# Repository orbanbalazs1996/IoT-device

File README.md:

# IoT-device
Lokális hálózatba szervezhető mérőpont tervezési fileok, reprezentéló oldalak.
Weboldal:
https://beta.dev.itk.ppke.hu/webprog/~orbba2/fooldal
Weboldal forráskód:
webpage_source.zip
Tok:
https://gmail851013.autodesk360.com/g/shares/SH919a0QTf3c32634dcfc6deb44a4809d65b?viewState=NoIgbgDAdAjCA0IDeAdEAXAngBwKZoC40ARXAZwEsBzAOzXjQEMyzd1C0YAzGAJgBMAzLgDGAWhgAWXAFYxk3pIhiAHJJEr5ATgBGO-o0mSAbCJha0AXxABdIA
Vezérlő programkód:
final.ino:
Tok nyomtatási file:
PCB_case.f3z
Mért adatok:
measured_data.zip
Képek:
pictures.zip
Kapcsolási tervrajz:
schema.sch
PCB tervrajz:
schema.brd

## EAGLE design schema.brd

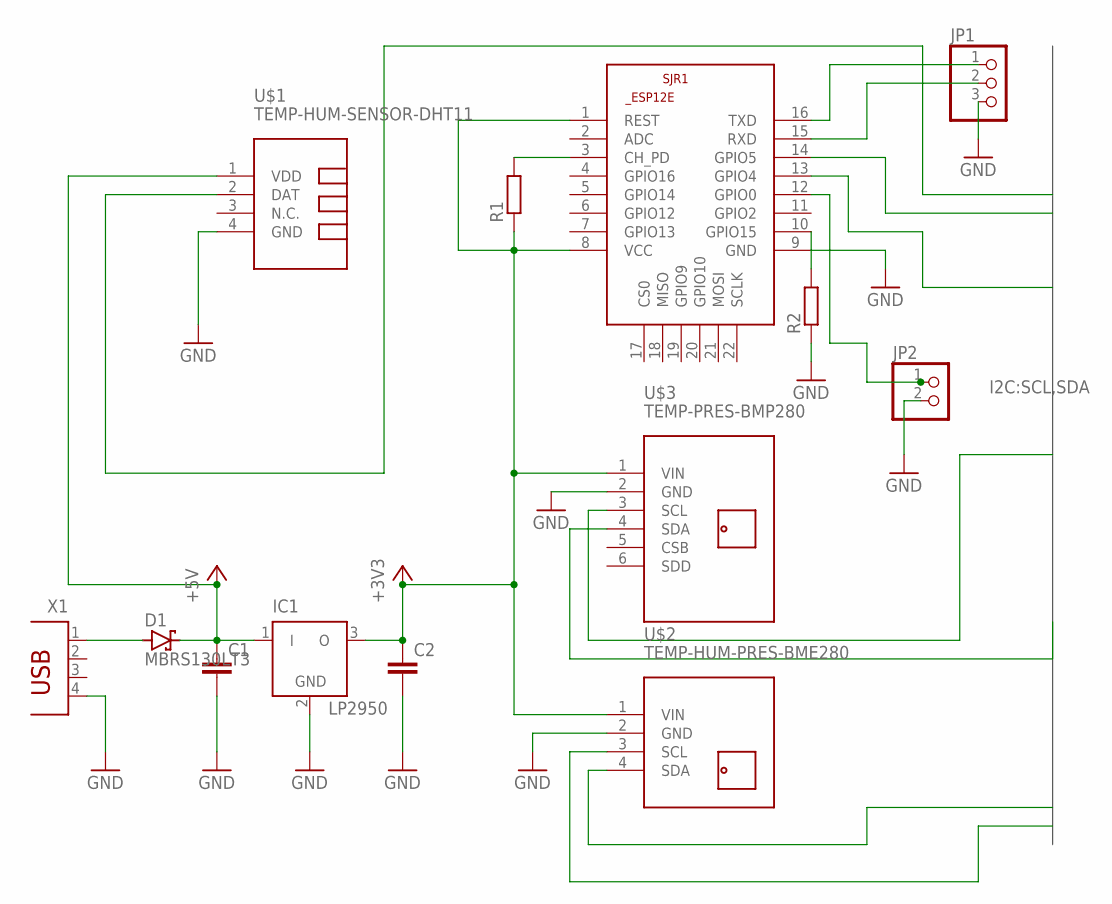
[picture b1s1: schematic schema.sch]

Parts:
C1, C2: C-EUC0603; C0603
D1: MBRS130LT3; SMB
IC1: LP2950; DPACK
JP1: PINHD-1X3; 1X03
JP2: PINHD-1X2; 1X02
R1, R2: R-EU_R0603; R0603
SJR1: ESP8266-12EESP12E; ESP8266-ESP12E
U$1: TEMP-HUM-SENSOR-DHT11
U$2: TEMP-HUM-PRES-BME280
U$3: TEMP-PRES-BMP280
X1: PN61729

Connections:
+3V3: C2.1, IC1.3 (O), R1.1, SJR1.1 (REST), SJR1.8 (VCC), U$2.1 (VIN), U$3.1 (VIN)
+5V: C1.1, D1.C, IC1.1 (I), U$1.1 (VDD)
GND: C1.2, C2.2, IC1.2 (GND), JP1.3, JP2.2, R2.1, SJR1.9 (GND), U$1.4 (GND), U$2.2 (GND), U$3.2 (GND), X1.4
unnamed: R1.2, SJR1.3 (CH_PD)
unnamed: JP2.1, SJR1.12 (GPIO0)
unnamed: D1.A, X1.1
unnamed: JP1.1, SJR1.16 (TXD)
unnamed: JP1.2, SJR1.15 (RXD)
unnamed: R2.2, SJR1.10 (GPIO15)
SCL: SJR1.14 (GPIO5), U$2.3 (SCL), U$3.3 (SCL)
SDA: SJR1.13 (GPIO4), U$1.2 (DAT), U$2.4 (SDA), U$3.4 (SDA)

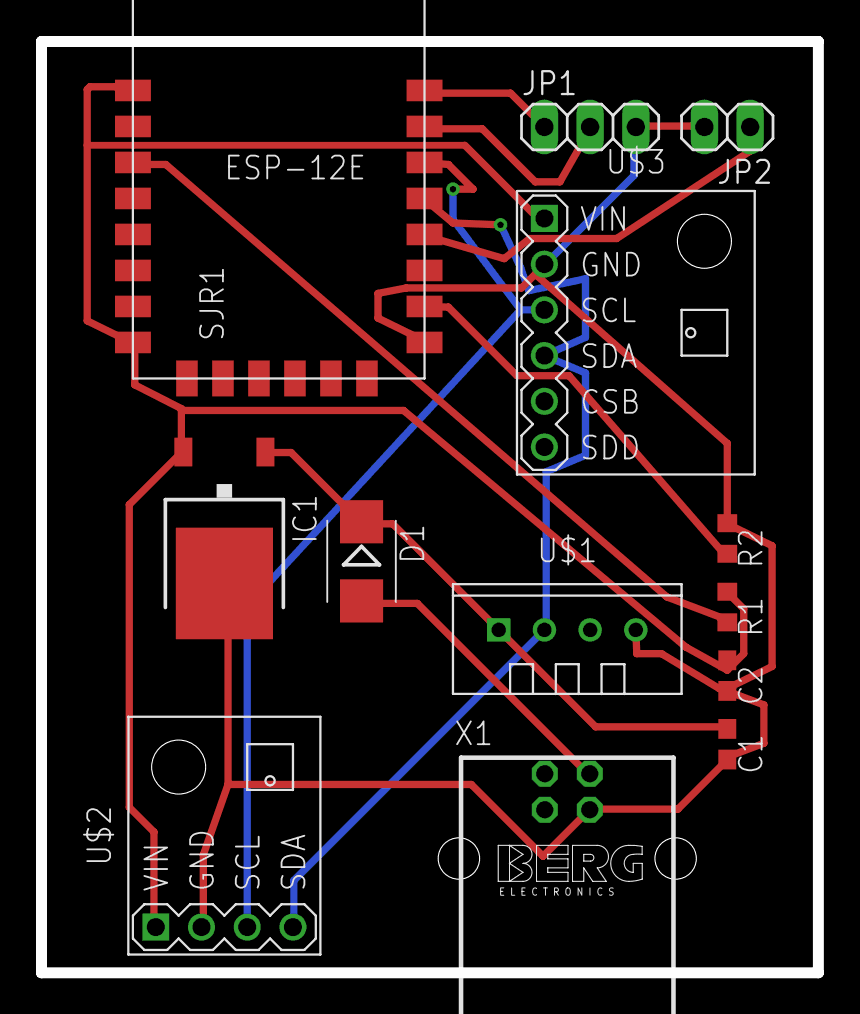
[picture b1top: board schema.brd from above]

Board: 2 copper layers, 43.2 x 51.7 mm, 13 parts (0 on the bottom side), 11 nets.

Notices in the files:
parts and their libraries:
diy-modules: Released under the Creative Commons Attribution 4.0 International License: http://creativecommons.org/licenses/by/4.0
